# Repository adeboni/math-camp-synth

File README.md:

# Burning Man Math Camp Synths
2022: Pendulum

2023: Jukebox

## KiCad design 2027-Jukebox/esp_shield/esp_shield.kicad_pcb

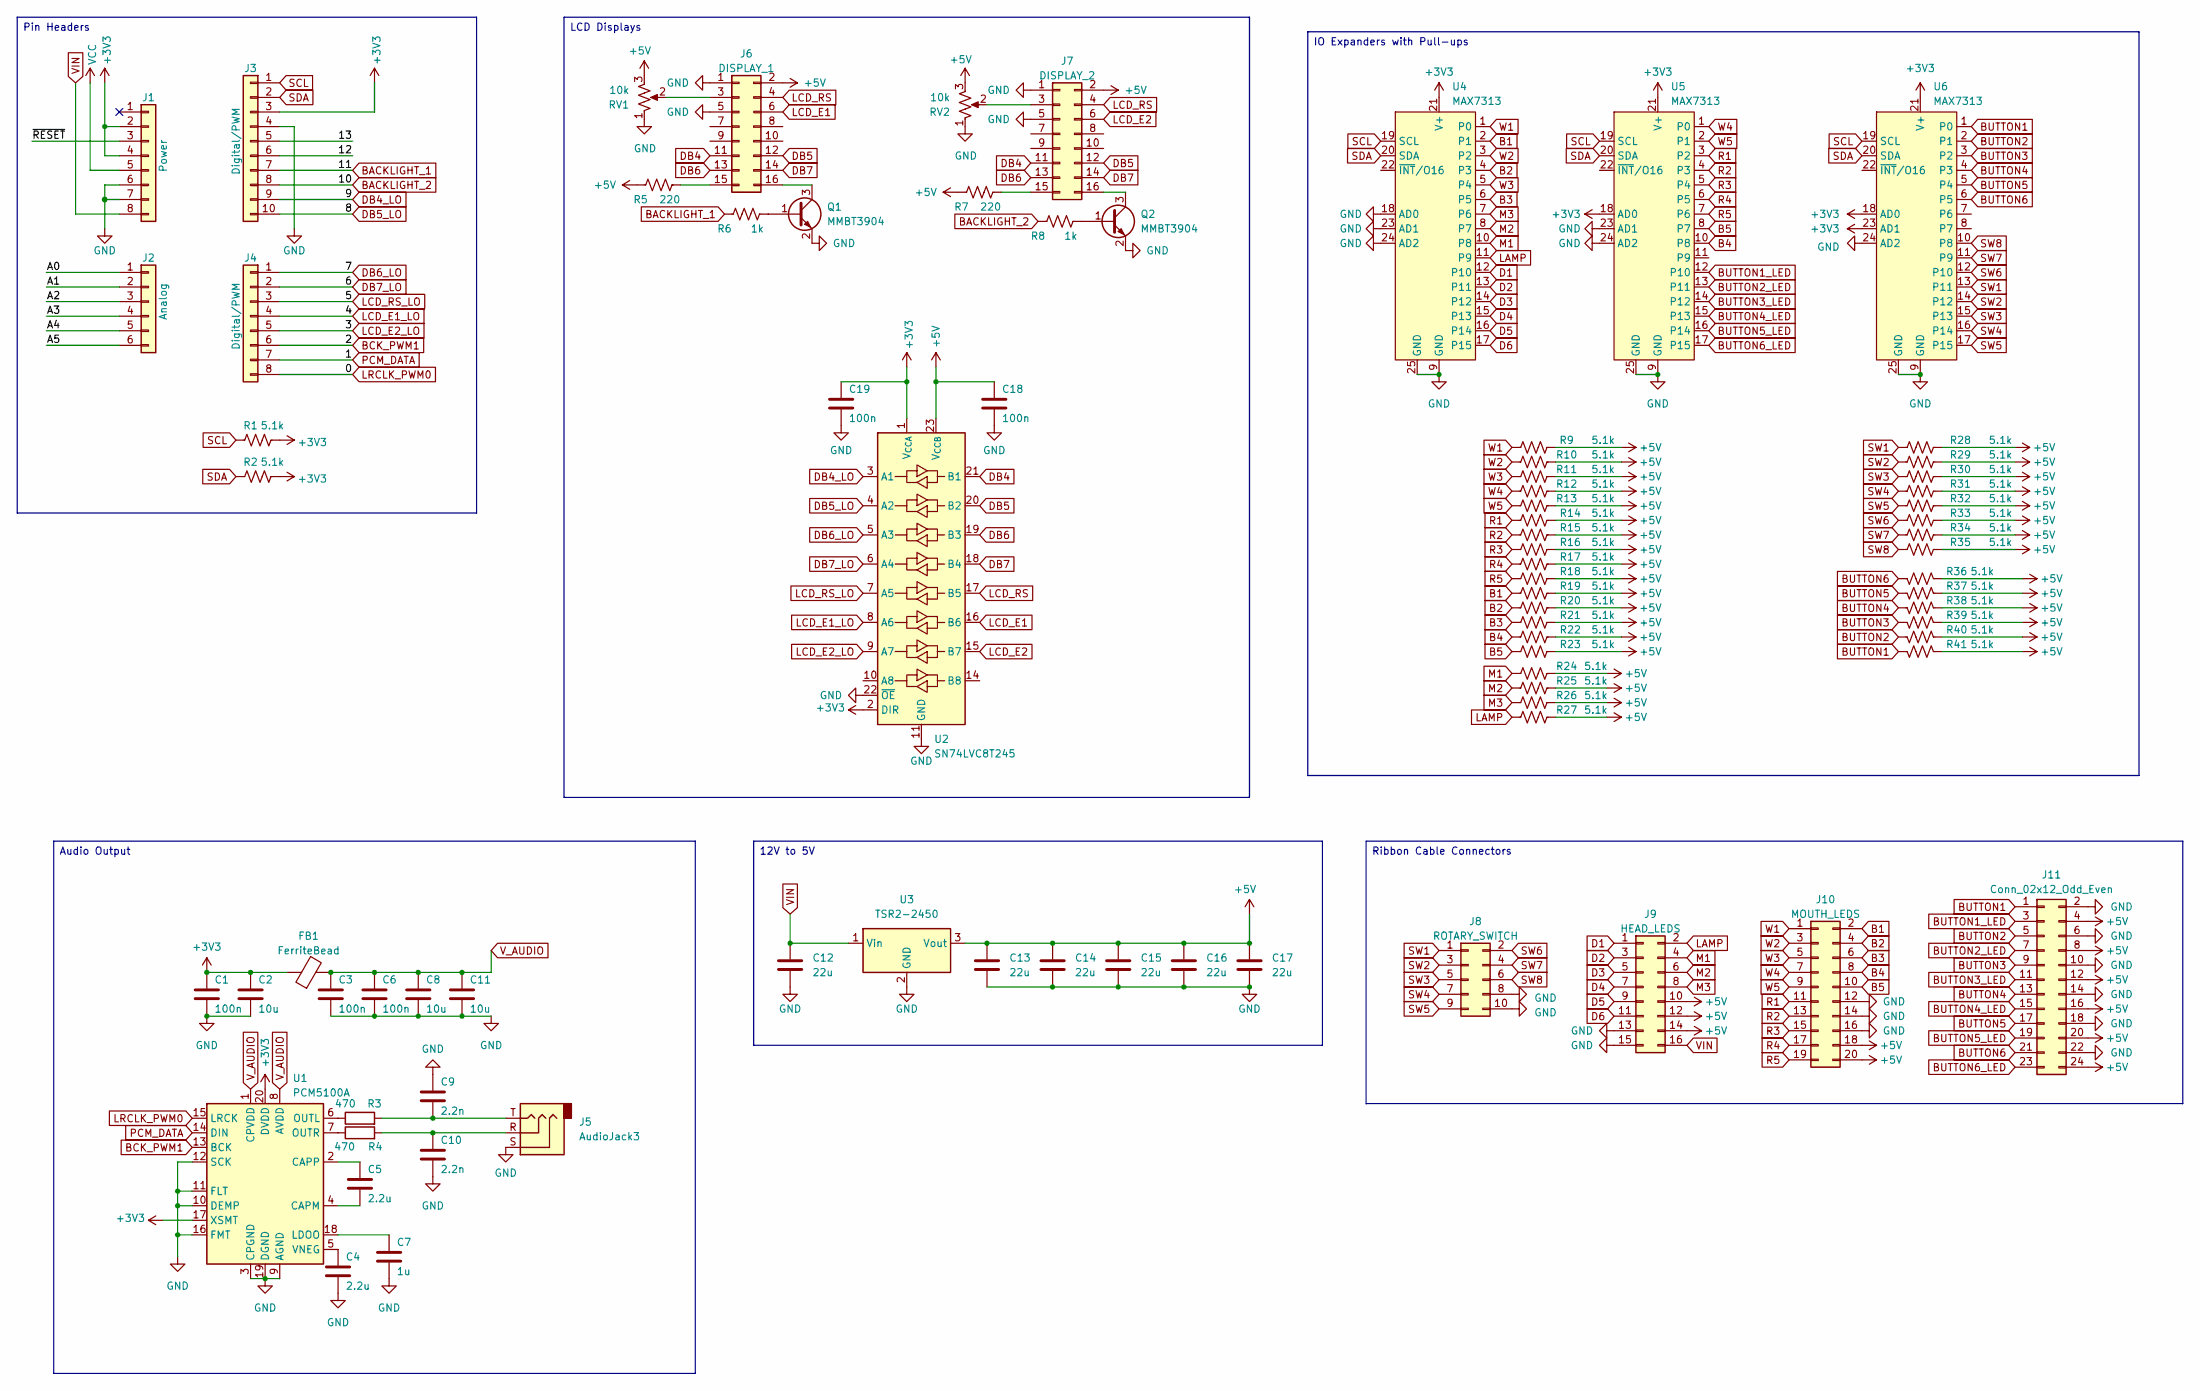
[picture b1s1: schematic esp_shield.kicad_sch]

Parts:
C1, C3, C6, C18, C19: 100n; C_0603_1608Metric
C2, C8, C11: 10u; C_0603_1608Metric
C4, C5: 2.2u; C_0603_1608Metric
C7: 1u; C_0603_1608Metric
C9, C10: 2.2n; C_0603_1608Metric
C12, C13, C14, C15, C16, C17: 22u; C_1206_3216Metric
FB1: FerriteBead; L_0603_1608Metric
J1: Power; PinSocket_1x08_P2.54mm_Vertical
J2: Analog; PinSocket_1x06_P2.54mm_Vertical
J3: Digital/PWM; PinSocket_1x10_P2.54mm_Vertical
J4: Digital/PWM; PinSocket_1x08_P2.54mm_Vertical
J5: AudioJack3; Jack_3.5mm_CUI_SJ-3523-SMT_Horizontal
J6: DISPLAY_1; IDC-Header_2x08_P2.54mm_Vertical
J7: DISPLAY_2; IDC-Header_2x08_P2.54mm_Vertical
J8: ROTARY_SWITCH; IDC-Header_2x05_P2.54mm_Vertical
J9: HEAD_LEDS; IDC-Header_2x08_P2.54mm_Vertical
J10: MOUTH_LEDS; IDC-Header_2x10_P2.54mm_Vertical
J11: Conn_02x12_Odd_Even; IDC-Header_2x12_P2.54mm_Vertical
Q1, Q2: MMBT3904; SOT-23
R1, R2, R9, R10, R11, R12, R13, R14, R15, R16, R17, R18, R19, R20, R21, R22, R23, R24, R25, R26, R27, R28, R29, R30, R31, R32, R33, R34, R35, R36, R37, R38, R39, R40, R41: 5.1k; R_0603_1608Metric
R3, R4: 470; R_0603_1608Metric
R5, R7: 220; R_0603_1608Metric
R6, R8: 1k; R_0603_1608Metric
RV1, RV2: 10k; Potentiometer_Bourns_3314G_Vertical
U1: PCM5100A; TSSOP-20_4.4x6.5mm_P0.65mm
U2: SN74LVC8T245; TSSOP-24_4.4x7.8mm_P0.65mm
U3: TSR2-2450; Converter_DCDC_TRACO_TSR2-xxxx_THT
U4, U5, U6: MAX7313; TQFN-24-1EP_4x4mm_P0.5mm_EP2.6x2.6mm_ThermalVias

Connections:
+3V3: C1.1, C2.1, C19.1, FB1.1, J1.2, J1.4, J3.3, R1.2, R2.2, U1.17 (XSMT), U1.20 (DVDD), U2.1 (V_{CCA}), U2.2 (DIR), U4.21 (V+), U5.18 (AD0), U5.21 (V+), U6.18 (AD0), U6.21 (V+), U6.23 (AD1)
+5V: C13.1, C14.1, C15.1, C16.1, C17.1, C18.1, J6.2, J7.2, J9.10, J9.12, J9.14, J10.18, J10.20, J11.4, J11.8, J11.12, J11.16, J11.20, J11.24, R5.1, R7.1, R9.2, R10.2, R11.2, R12.2, R13.2, R14.2, R15.2, R16.2, R17.2, R18.2, R19.2, R20.2, R21.2, R22.2, R23.2, R24.2, R25.2, R26.2, R27.2, R28.2, R29.2, R30.2, R31.2, R32.2, R33.2, R34.2, R35.2, R36.2, R37.2, R38.2, R39.2, R40.2, R41.2, RV1.3, RV2.3, U2.23 (V_{CCB}), U2.24 (V_{CCB}), U3.3 (Vout)
/12: J3.6
/13: J3.5
/A0: J2.1
/A1: J2.2
/A2: J2.3
/A3: J2.4
/A4: J2.5
/A5: J2.6
/~RESET: J1.3
B1: J10.2, R19.1, U4.2 (P1)
B2: J10.4, R20.1, U4.4 (P3)
B3: J10.6, R21.1, U4.6 (P5)
B4: J10.8, R22.1, U5.10 (P8)
B5: J10.10, R23.1, U5.8 (P7)
BACKLIGHT_1: J3.7, R6.1
BACKLIGHT_2: J3.8, R8.1
BCK_PWM1: J4.6, U1.13 (BCK)
BUTTON1: J11.1, R41.1, U6.1 (P0)
BUTTON1_LED: J11.3, U5.12 (P10)
BUTTON2: J11.5, R40.1, U6.2 (P1)
BUTTON2_LED: J11.7, U5.13 (P11)
BUTTON3: J11.9, R39.1, U6.3 (P2)
BUTTON3_LED: J11.11, U5.14 (P12)
BUTTON4: J11.13, R38.1, U6.4 (P3)
BUTTON4_LED: J11.15, U5.15 (P13)
BUTTON5: J11.17, R37.1, U6.5 (P4)
BUTTON5_LED: J11.19, U5.16 (P14)
BUTTON6: J11.21, R36.1, U6.6 (P5)
BUTTON6_LED: J11.23, U5.17 (P15)
D1: J9.1, U4.12 (P10)
D2: J9.3, U4.13 (P11)
D3: J9.5, U4.14 (P12)
D4: J9.7, U4.15 (P13)
D5: J9.9, U4.16 (P14)
D6: J9.11, U4.17 (P15)
DB4: J6.11, J7.11, U2.21 (B1)
DB4_LO: J3.9, U2.3 (A1)
DB5: J6.12, J7.12, U2.20 (B2)
DB5_LO: J3.10, U2.4 (A2)
DB6: J6.13, J7.13, U2.19 (B3)
DB6_LO: J4.1, U2.5 (A3)
DB7: J6.14, J7.14, U2.18 (B4)
DB7_LO: J4.2, U2.6 (A4)
GND: C1.2, C2.2, C3.2, C4.2, C6.2, C7.2, C8.2, C9.1, C10.2, C11.2, C12.2, C13.2, C14.2, C15.2, C16.2, C17.2, C18.2, C19.2, J1.6, J1.7, J3.4, J5.S, J6.1, J6.5, J7.1, J7.5, J8.8, J8.10, J9.13, J9.15, J10.12, J10.14, J10.16, J11.2, J11.6, J11.10, J11.14, J11.18, J11.22, Q1.2 (E), Q2.2 (E), RV1.1, RV2.1, U1.3 (CPGND), U1.9 (AGND), U1.10 (DEMP), U1.11 (FLT), U1.12 (SCK), U1.16 (FMT), U1.19 (DGND), U2.11 (GND), U2.12 (GND), U2.13 (GND), U2.22 (~OE), U3.2 (GND), U4.9 (GND), U4.18 (AD0), U4.23 (AD1), U4.24 (AD2), U4.25 (GND), U5.9 (GND), U5.23 (AD1), U5.24 (AD2), U5.25 (GND), U6.9 (GND), U6.24 (AD2), U6.25 (GND)
LAMP: J9.2, R27.1, U4.11 (P9)
LCD_E1: J6.6, U2.16 (B6)
LCD_E1_LO: J4.4, U2.8 (A6)
LCD_E2: J7.6, U2.15 (B7)
LCD_E2_LO: J4.5, U2.9 (A7)
LCD_RS: J6.4, J7.4, U2.17 (B5)
LCD_RS_LO: J4.3, U2.7 (A5)
LRCLK_PWM0: J4.8, U1.15 (LRCK)
M1: J9.4, R24.1, U4.10 (P8)
M2: J9.6, R25.1, U4.8 (P7)
M3: J9.8, R26.1, U4.7 (P6)
unnamed: C9.2, J5.T, R3.2
unnamed: C10.1, J5.R, R4.2
unnamed: J6.3, RV1.2
unnamed: J6.15, R5.2
unnamed: J6.16, Q1.3 (C)
unnamed: J7.3, RV2.2
unnamed: J7.15, R7.2
unnamed: J7.16, Q2.3 (C)
unnamed: Q1.1 (B), R6.2
unnamed: Q2.1 (B), R8.2
unnamed: C5.2, U1.4 (CAPM)
unnamed: C5.1, U1.2 (CAPP)
unnamed: C7.1, U1.18 (LDOO)
unnamed: R3.1, U1.6 (OUTL)
unnamed: R4.1, U1.7 (OUTR)
unnamed: C4.1, U1.5 (VNEG)
PCM_DATA: J4.7, U1.14 (DIN)
R1: J10.11, R14.1, U5.3 (P2)
R2: J10.13, R15.1, U5.4 (P3)
R3: J10.15, R16.1, U5.5 (P4)
R4: J10.17, R17.1, U5.6 (P5)
R5: J10.19, R18.1, U5.7 (P6)
SCL: J3.1, R1.1, U4.19 (SCL), U5.19 (SCL), U6.19 (SCL)
SDA: J3.2, R2.1, U4.20 (SDA), U5.20 (SDA), U6.20 (SDA)
SW1: J8.1, R28.1, U6.13 (P11)
SW2: J8.3, R29.1, U6.14 (P12)
SW3: J8.5, R30.1, U6.15 (P13)
SW4: J8.7, R31.1, U6.16 (P14)
SW5: J8.9, R32.1, U6.17 (P15)
SW6: J8.2, R33.1, U6.12 (P10)
SW7: J8.4, R34.1, U6.11 (P9)
SW8: J8.6, R35.1, U6.10 (P8)
VCC: J1.5
VIN: C12.1, J1.8, J9.16, U3.1 (Vin)
V_AUDIO: C3.1, C6.1, C8.1, C11.1, FB1.2, U1.1 (CPVDD), U1.8 (AVDD)
W1: J10.1, R9.1, U4.1 (P0)
W2: J10.3, R10.1, U4.3 (P2)
W3: J10.5, R11.1, U4.5 (P4)
W4: J10.7, R12.1, U5.1 (P0)
W5: J10.9, R13.1, U5.2 (P1)

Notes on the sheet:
Ribbon Cable Connectors
LCD Displays
IO Expanders with Pull-ups
12V to 5V
Audio Output
Pin Headers

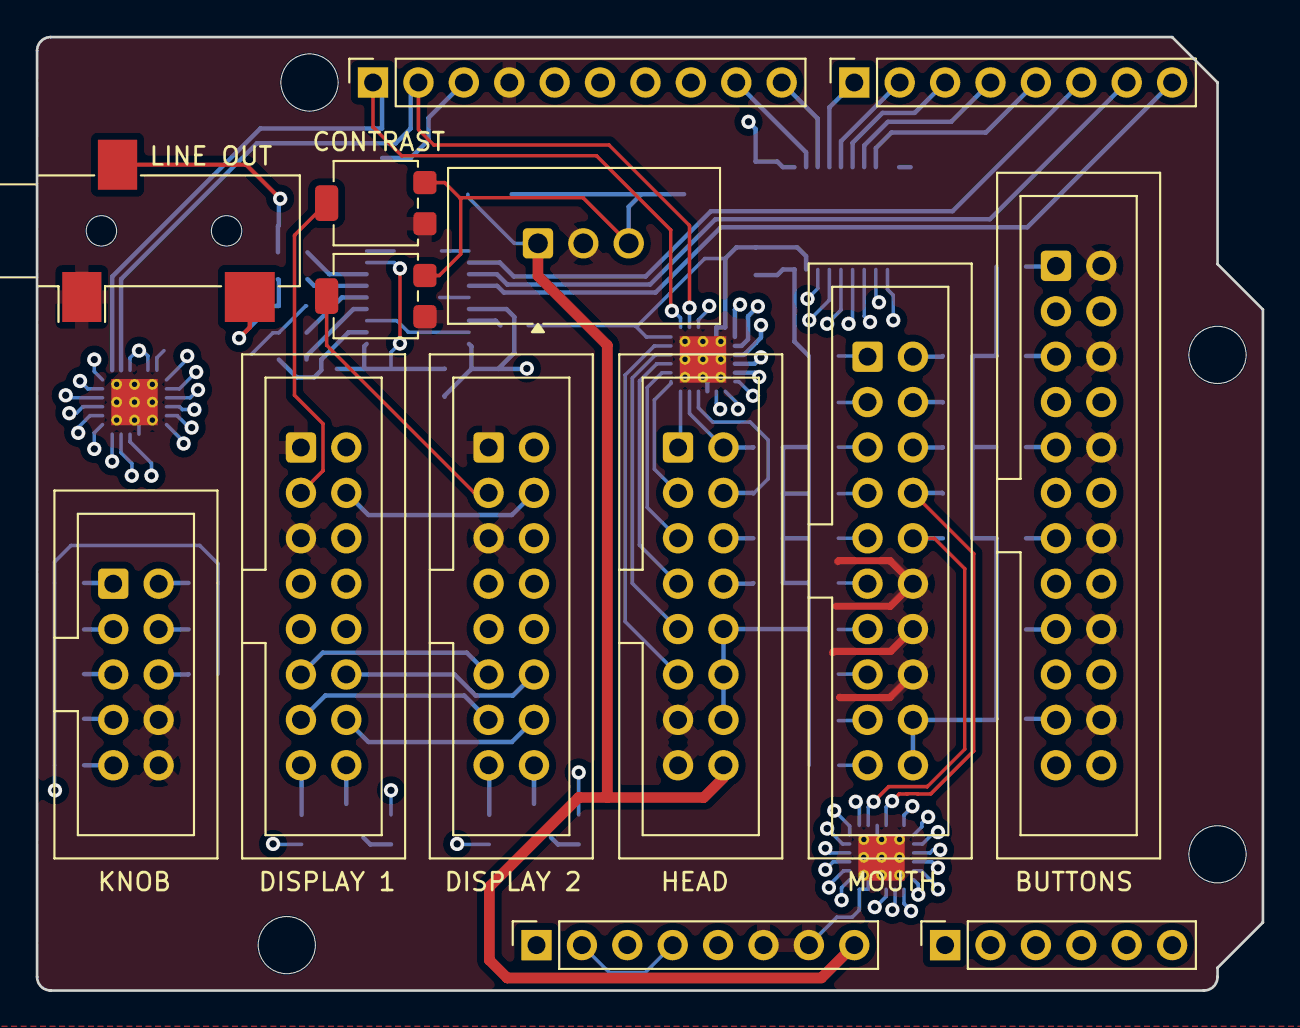
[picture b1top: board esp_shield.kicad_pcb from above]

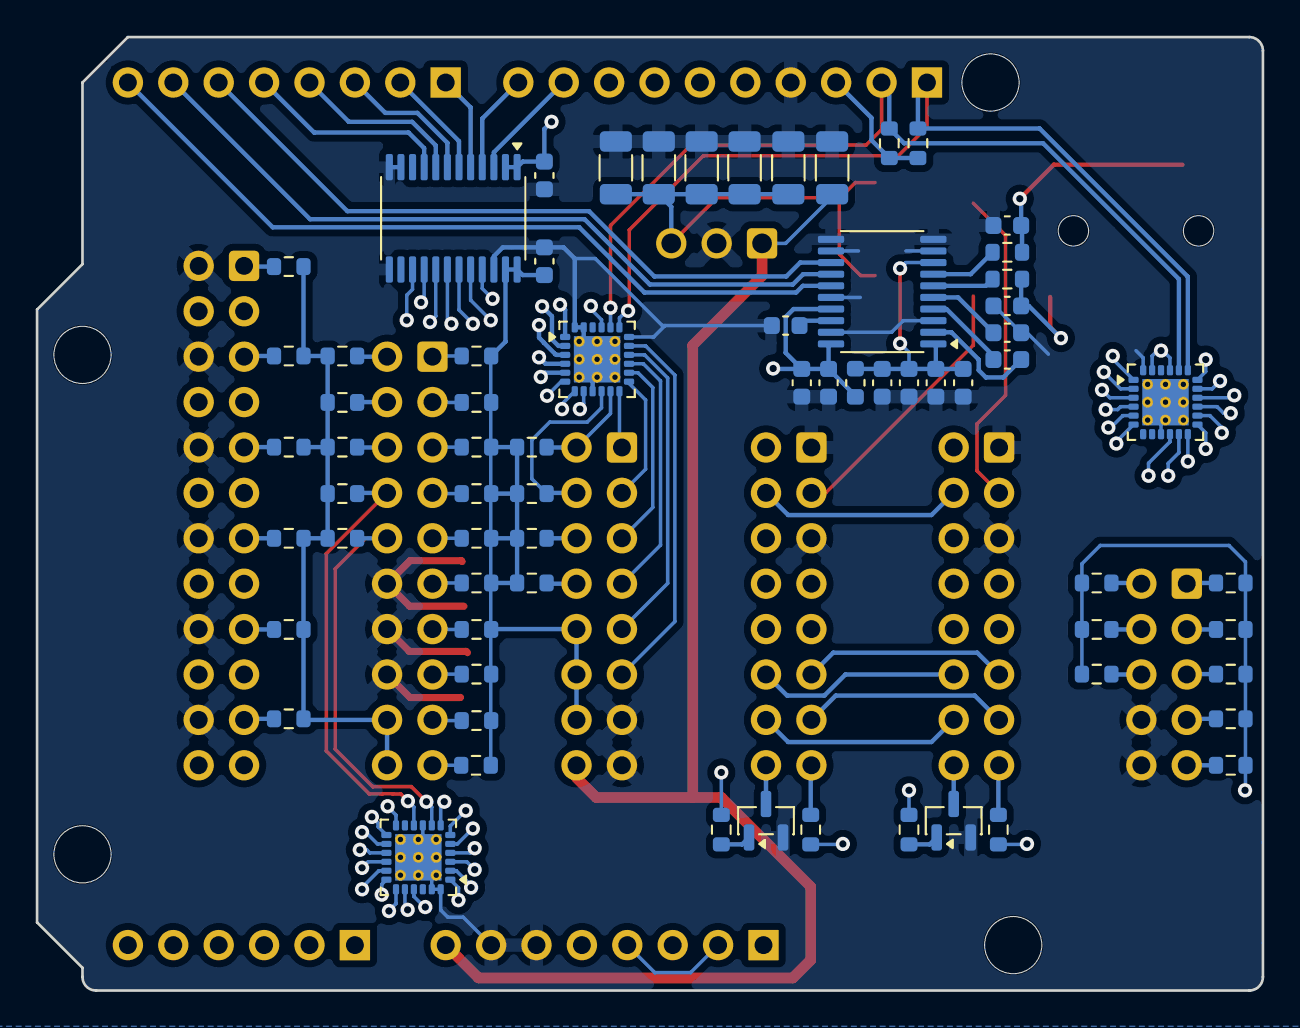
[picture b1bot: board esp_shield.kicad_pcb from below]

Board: 4 copper layers, 68.6 x 53.3 mm, 86 parts (68 on the bottom side), 87 nets.

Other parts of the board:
MH1, MH2, MH3, MH4: MountingHole_3.2mm

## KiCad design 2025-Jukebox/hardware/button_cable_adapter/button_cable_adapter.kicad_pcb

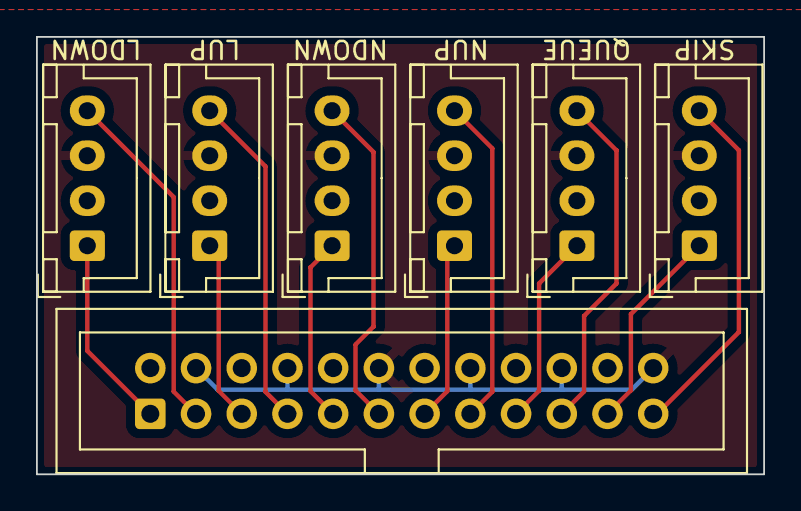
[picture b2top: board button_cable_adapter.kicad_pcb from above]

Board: 2 copper layers, 40.4 x 24.3 mm, 7 parts (0 on the bottom side), 14 nets.

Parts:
J1: Conn_02x12_Odd_Even; IDC-Header_2x12_P2.54mm_Vertical
J2: BUTTON_1; JST_XH_B4B-XH-A_1x04_P2.50mm_Vertical
J3: BUTTON_5; JST_XH_B4B-XH-A_1x04_P2.50mm_Vertical
J4: BUTTON_2; JST_XH_B4B-XH-A_1x04_P2.50mm_Vertical
J5: BUTTON_6; JST_XH_B4B-XH-A_1x04_P2.50mm_Vertical
J6: BUTTON_3; JST_XH_B4B-XH-A_1x04_P2.50mm_Vertical
J8: BUTTON_4; JST_XH_B4B-XH-A_1x04_P2.50mm_Vertical

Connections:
+5V: J1.4, J1.8, J1.12, J1.16, J1.20, J1.24, J2.3, J3.3, J4.3, J5.3, J6.3, J8.3
BUTTON1: J1.1, J2.1
BUTTON1_LED: J1.3, J2.4
BUTTON2: J1.5, J4.1
BUTTON2_LED: J1.7, J4.4
BUTTON3: J1.9, J6.1
BUTTON3_LED: J1.11, J6.4
BUTTON4: J1.13, J8.1
BUTTON4_LED: J1.15, J8.4
BUTTON5: J1.17, J3.1
BUTTON5_LED: J1.19, J3.4
BUTTON6: J1.21, J5.1
BUTTON6_LED: J1.23, J5.4
GND: J1.2, J1.6, J1.10, J1.14, J1.18, J1.22, J2.2, J3.2, J4.2, J5.2, J6.2, J8.2

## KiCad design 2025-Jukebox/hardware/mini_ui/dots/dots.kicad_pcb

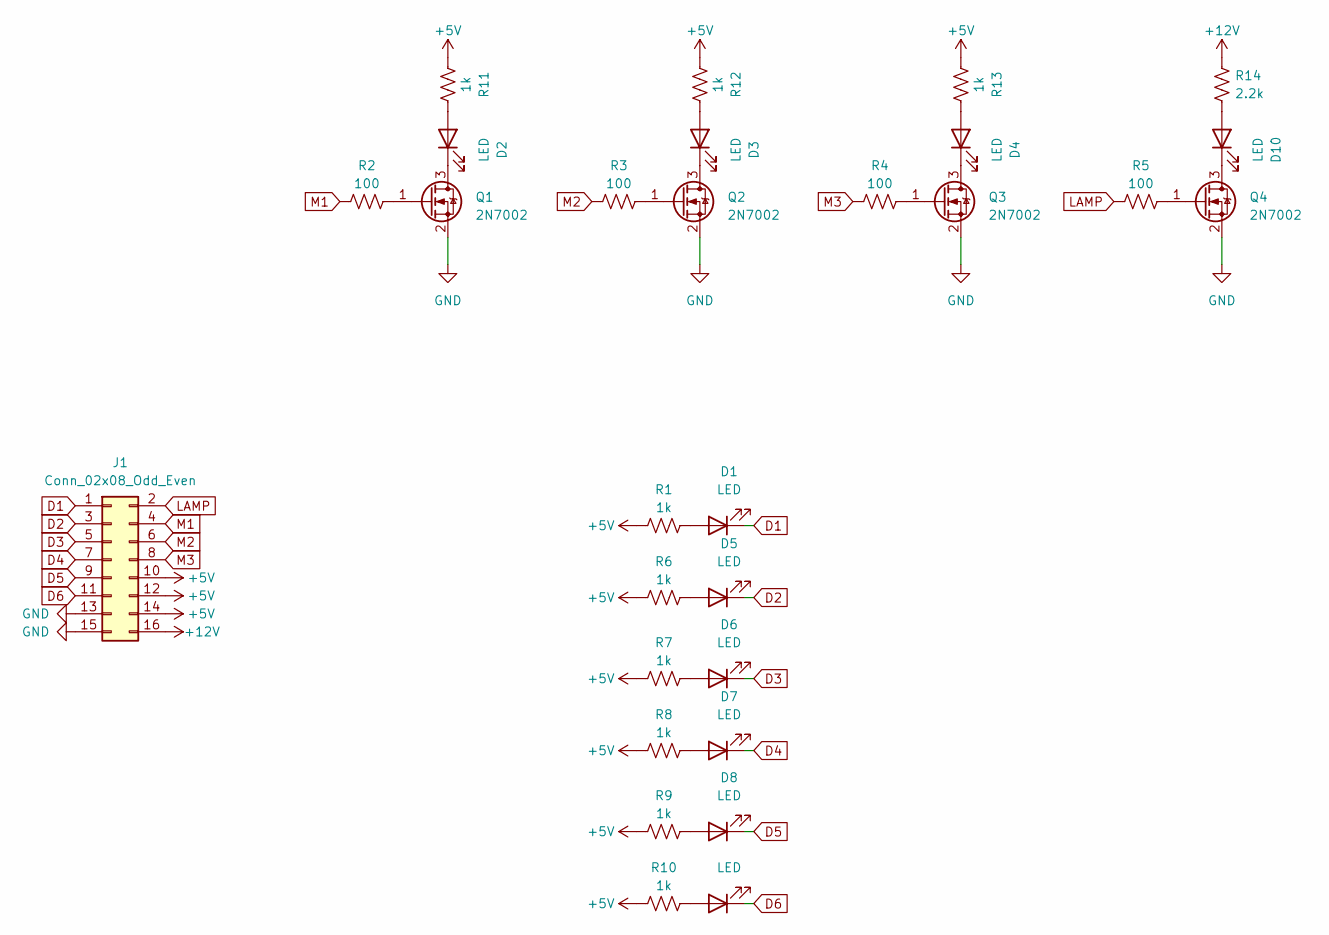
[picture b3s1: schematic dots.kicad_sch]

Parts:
D1, D2, D3, D4, D5, D6, D7, D8, D9, D10: LED; LED_0603_1608Metric
J1: Conn_02x08_Odd_Even; PinSocket_2x08_P2.54mm_Vertical_SMD
Q1, Q2, Q3, Q4: 2N7002; SOT-23
R1, R6, R7, R8, R9, R10, R11, R12, R13: 1k; R_0603_1608Metric
R2, R3, R4, R5: 100; R_0603_1608Metric
R14: 2.2k; R_0603_1608Metric

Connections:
+5V: J1.10, J1.12, J1.14, R1.1, R6.1, R7.1, R8.1, R9.1, R10.1, R11.1, R12.1, R13.1
+12V: J1.16, R14.1
D1: D1.1 (K), J1.1
D2: D5.1 (K), J1.3
D3: D6.1 (K), J1.5
D4: D7.1 (K), J1.7
D5: D8.1 (K), J1.9
D6: D9.1 (K), J1.11
GND: J1.13, J1.15, Q1.2 (S), Q2.2 (S), Q3.2 (S), Q4.2 (S)
LAMP: J1.2, R5.1
M1: J1.4, R2.1
M2: J1.6, R3.1
M3: J1.8, R4.1
unnamed: D1.2 (A), R1.2
unnamed: D2.2 (A), R11.2
unnamed: D2.1 (K), Q1.3 (D)
unnamed: D3.2 (A), R12.2
unnamed: D3.1 (K), Q2.3 (D)
unnamed: D4.2 (A), R13.2
unnamed: D4.1 (K), Q3.3 (D)
unnamed: D5.2 (A), R6.2
unnamed: D6.2 (A), R7.2
unnamed: D7.2 (A), R8.2
unnamed: D8.2 (A), R9.2
unnamed: D9.2 (A), R10.2
unnamed: D10.2 (A), R14.2
unnamed: D10.1 (K), Q4.3 (D)
unnamed: Q1.1 (G), R2.2
unnamed: Q2.1 (G), R3.2
unnamed: Q3.1 (G), R4.2
unnamed: Q4.1 (G), R5.2

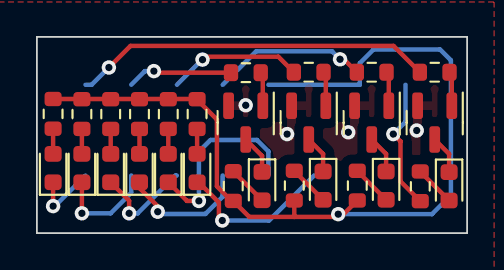
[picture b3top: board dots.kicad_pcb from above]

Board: 2 copper layers, 23.9 x 10.9 mm, 29 parts (1 on the bottom side), 31 nets.

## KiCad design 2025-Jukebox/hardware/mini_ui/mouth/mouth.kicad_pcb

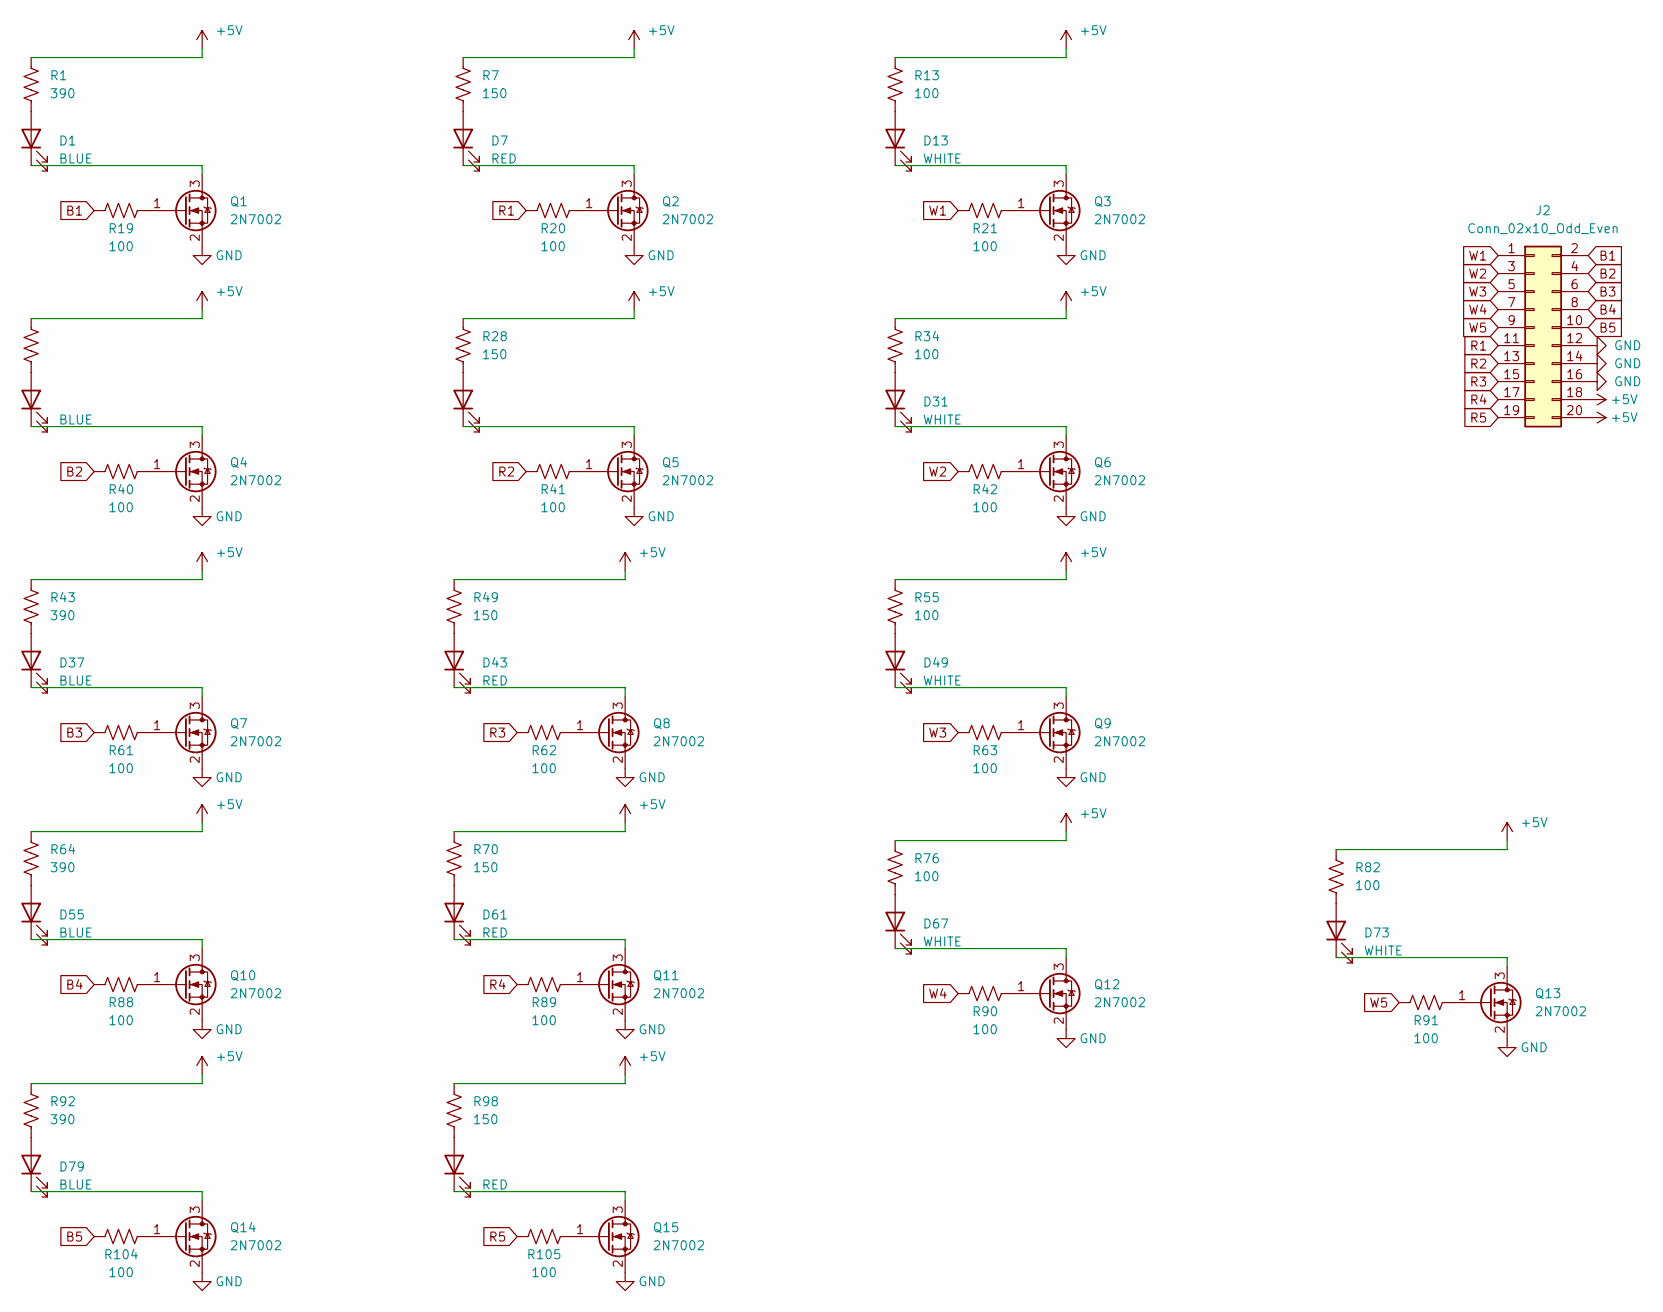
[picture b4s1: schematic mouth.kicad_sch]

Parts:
D1, D19, D37, D55, D79: BLUE; LED_0603_1608Metric
D7, D25, D43, D61, D85: RED; LED_0603_1608Metric
D13, D31, D49, D67, D73: WHITE; LED_0603_1608Metric
J2: Conn_02x10_Odd_Even; PinSocket_2x10_P2.54mm_Vertical_SMD
Q1, Q2, Q3, Q4, Q5, Q6, Q7, Q8, Q9, Q10, Q11, Q12, Q13, Q14, Q15: 2N7002; SOT-23
R1, R22, R43, R64, R92: 390; R_0603_1608Metric
R7, R28, R49, R70, R98: 150; R_0603_1608Metric
R13, R19, R20, R21, R34, R40, R41, R42, R55, R61, R62, R63, R76, R82, R88, R89, R90, R91, R104, R105: 100; R_0603_1608Metric

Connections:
+5V: J2.18, J2.20, R1.2, R7.2, R13.2, R22.2, R28.2, R34.2, R43.2, R49.2, R55.2, R64.2, R70.2, R76.2, R82.2, R92.2, R98.2
B1: J2.2, R19.1
B2: J2.4, R40.1
B3: J2.6, R61.1
B4: J2.8, R88.1
B5: J2.10, R104.1
GND: J2.12, J2.14, J2.16, Q1.2 (S), Q2.2 (S), Q3.2 (S), Q4.2 (S), Q5.2 (S), Q6.2 (S), Q7.2 (S), Q8.2 (S), Q9.2 (S), Q10.2 (S), Q11.2 (S), Q12.2 (S), Q13.2 (S), Q14.2 (S), Q15.2 (S)
unnamed: D1.2 (A), R1.1
unnamed: D1.1 (K), Q1.3 (D)
unnamed: D7.2 (A), R7.1
unnamed: D7.1 (K), Q2.3 (D)
unnamed: D13.2 (A), R13.1
unnamed: D13.1 (K), Q3.3 (D)
unnamed: D19.2 (A), R22.1
unnamed: D19.1 (K), Q4.3 (D)
unnamed: D25.2 (A), R28.1
unnamed: D25.1 (K), Q5.3 (D)
unnamed: D31.2 (A), R34.1
unnamed: D31.1 (K), Q6.3 (D)
unnamed: D37.2 (A), R43.1
unnamed: D37.1 (K), Q7.3 (D)
unnamed: D43.2 (A), R49.1
unnamed: D43.1 (K), Q8.3 (D)
unnamed: D49.2 (A), R55.1
unnamed: D49.1 (K), Q9.3 (D)
unnamed: D55.2 (A), R64.1
unnamed: D55.1 (K), Q10.3 (D)
unnamed: D61.2 (A), R70.1
unnamed: D61.1 (K), Q11.3 (D)
unnamed: D67.2 (A), R76.1
unnamed: D67.1 (K), Q12.3 (D)
unnamed: D73.2 (A), R82.1
unnamed: D73.1 (K), Q13.3 (D)
unnamed: D79.2 (A), R92.1
unnamed: D79.1 (K), Q14.3 (D)
unnamed: D85.2 (A), R98.1
unnamed: D85.1 (K), Q15.3 (D)
unnamed: Q1.1 (G), R19.2
unnamed: Q2.1 (G), R20.2
unnamed: Q3.1 (G), R21.2
unnamed: Q4.1 (G), R40.2
unnamed: Q5.1 (G), R41.2
unnamed: Q6.1 (G), R42.2
unnamed: Q7.1 (G), R61.2
unnamed: Q8.1 (G), R62.2
unnamed: Q9.1 (G), R63.2
unnamed: Q10.1 (G), R88.2
unnamed: Q11.1 (G), R89.2
unnamed: Q12.1 (G), R90.2
unnamed: Q13.1 (G), R91.2
unnamed: Q14.1 (G), R104.2
unnamed: Q15.1 (G), R105.2
R1: J2.11, R20.1
R2: J2.13, R41.1
R3: J2.15, R62.1
R4: J2.17, R89.1
R5: J2.19, R105.1
W1: J2.1, R21.1
W2: J2.3, R42.1
W3: J2.5, R63.1
W4: J2.7, R90.1
W5: J2.9, R91.1

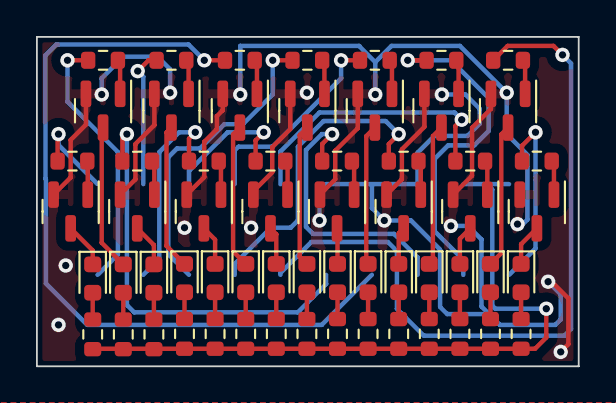
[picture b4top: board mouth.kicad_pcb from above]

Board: 2 copper layers, 30.1 x 18.3 mm, 61 parts (1 on the bottom side), 62 nets.

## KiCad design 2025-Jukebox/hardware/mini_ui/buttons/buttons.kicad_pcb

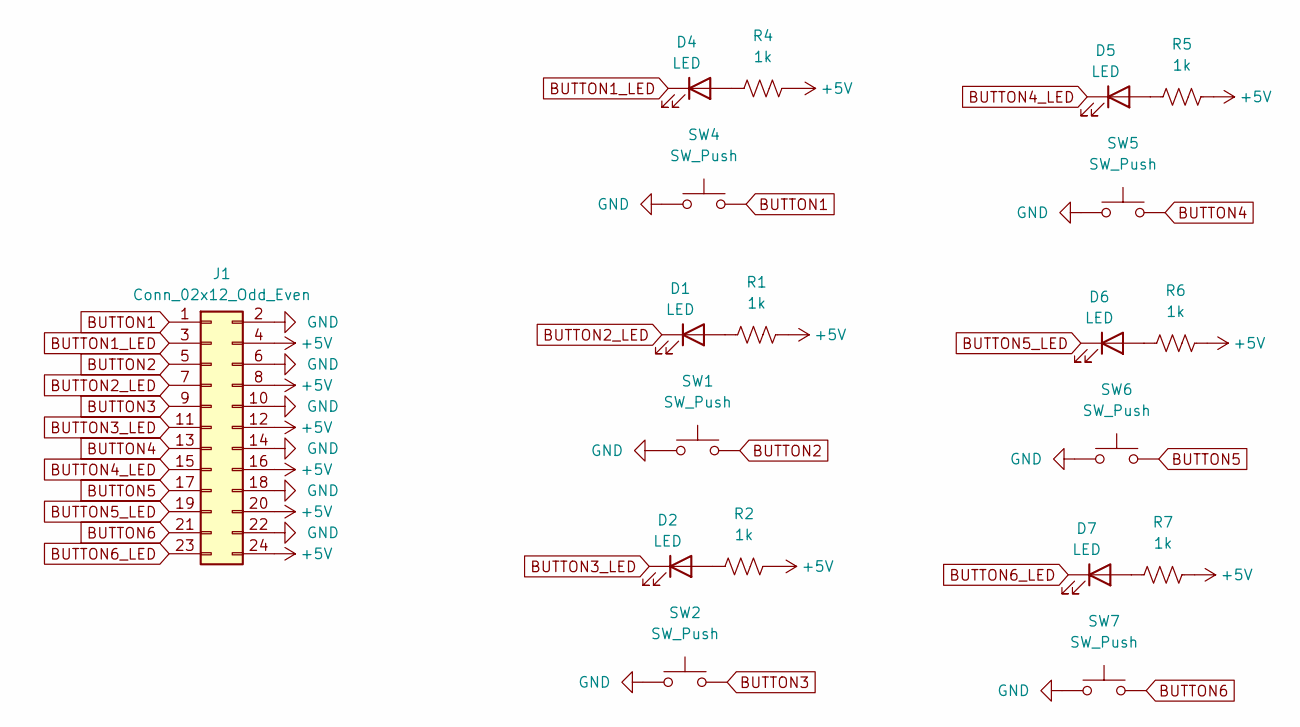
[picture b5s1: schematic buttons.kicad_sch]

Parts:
D1, D2, D4, D5, D6, D7: LED; LED_0603_1608Metric
J1: Conn_02x12_Odd_Even; PinSocket_2x12_P2.54mm_Vertical_SMD
R1, R2, R4, R5, R6, R7: 1k; R_0603_1608Metric
SW1, SW2, SW4, SW5, SW6, SW7: SW_Push; SW_Push_SPST_NO_Alps_SKRK

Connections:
+5V: J1.4, J1.8, J1.12, J1.16, J1.20, J1.24, R1.2, R2.2, R4.2, R5.2, R6.2, R7.2
BUTTON1: J1.1, SW4.2
BUTTON1_LED: D4.1 (K), J1.3
BUTTON2: J1.5, SW1.2
BUTTON2_LED: D1.1 (K), J1.7
BUTTON3: J1.9, SW2.2
BUTTON3_LED: D2.1 (K), J1.11
BUTTON4: J1.13, SW5.2
BUTTON4_LED: D5.1 (K), J1.15
BUTTON5: J1.17, SW6.2
BUTTON5_LED: D6.1 (K), J1.19
BUTTON6: J1.21, SW7.2
BUTTON6_LED: D7.1 (K), J1.23
GND: J1.2, J1.6, J1.10, J1.14, J1.18, J1.22, SW1.1, SW2.1, SW4.1, SW5.1, SW6.1, SW7.1
unnamed: D1.2 (A), R1.1
unnamed: D2.2 (A), R2.1
unnamed: D4.2 (A), R4.1
unnamed: D5.2 (A), R5.1
unnamed: D6.2 (A), R6.1
unnamed: D7.2 (A), R7.1

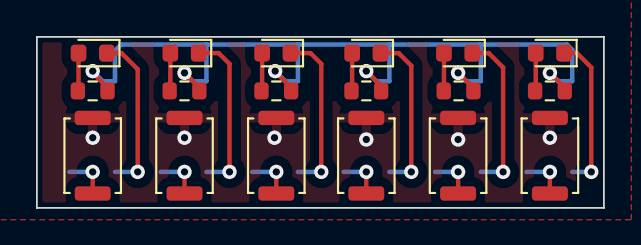
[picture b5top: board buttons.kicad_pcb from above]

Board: 2 copper layers, 31.5 x 9.5 mm, 19 parts (1 on the bottom side), 20 nets.
